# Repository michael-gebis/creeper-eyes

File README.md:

# Frankenstein Head with Animated Eyes

Twin animated eyes for Jose Aveleira's 3D-printed
[Frankenstein head with animated eyes](https://www.printables.com/model/620191-frankenstein-head-with-animated-eyes),
driven by an ESP32 and two 1.5" OLED panels.

The eyes wander, blink and dilate on their own, and keep doing it with nothing
plugged in but power. Everything past that is optional.

## What it does

- **Twenty-five eye designs** — [see them all](docs/EYES.md). One is built in; any other can be
  loaded from a file on the control page, [no rebuild needed](docs/EYE_FILES.md)
- **Watches the room on its own**: wandering gaze, autonomous blinking, pupils
  that dilate
- **Takes direction** from a web page, a serial console or a REST API, so you
  can aim the gaze or fire a startle effect without opening the head
- **Tells the time**, with an analogue clock drawn in the iris
- **Sleeps at night**, so it is not staring at 3am
- **Dims to suit the room**, fading between levels, and switches right off —
  [brightness](docs/BRIGHTNESS.md)
- **Sets itself up from a code on the eye** — point a phone at it and it
  joins the head's network and opens the setup page, with nothing typed
- **Updates over WiFi**, so a sealed head never needs opening again
- **Runs on a generic ESP32** and either colour or greyscale panels

Two panels, one dev board, fourteen wires. If you would rather not have the
wires, there is [a circuit board](hardware/README.md) for it.

## What to buy

### ESP32 board

Any **classic ESP32** (ESP-WROOM-32 module, Xtensa dual core) with 4 MB flash.

> **Not** an ESP32-**S2**, **S3**, **C3** or **C6**. Those are different
> architectures and will not run this build. If your board shows up as USB
> vendor ID `303A`, it is one of those. A classic ESP32 uses a separate
> USB-serial chip — CH340 (`1A86`) or CP210x (`10C4`).

Known good: the 30-pin **DOIT ESP32 DevKit V1**, sold under a dozen names with
"NodeMCU", "ESP32S" and "Type-C" in the title. Roughly $5 each in three-packs.
Either USB-serial chip is fine; CH340 may need a driver on Windows.

### Displays — read this part carefully

Waveshare sells **two different 1.5" 128×128 OLED modules** with nearly
identical names and **identical 7-pin headers**. You cannot tell them apart by
wiring, and the wrong one shows white static.

| Product | Controller | Display | Build to use |
| :------ | :--------- | :------ | :----------- |
| **1.5inch RGB OLED Module** | SSD1351 | 65K colour | `esp32dev` |
| **1.5inch OLED Module** | SSD1327 | 16 greys | `gray` |

Buy **two**. Either works, and the grayscale panels run faster.

Which to get depends on the eyes you want. The artwork was drawn in colour,
and **some designs do not survive the conversion** — anything carrying its
detail in hue rather than in brightness comes out flat. The newt is the worst
of them: its greens and golds land on much the same grey. Others lose nothing
worth having; the default eye in particular looks every bit as good in
sixteen greys as it does in colour.

[docs/EYES.md](docs/EYES.md) renders all 25 designs both ways, side by side,
which is the quickest way to decide.

Both are 3.3 V / 5 V tolerant and need no level shifting.

### Everything else

- Breadboard and male-to-female jumper wires (14 connections)
- USB-C cable — this also carries the serial console
- The printed parts and hardware from the
  [Printables model](https://www.printables.com/model/620191-frankenstein-head-with-animated-eyes)

A plain USB port powers everything comfortably: two panels and the ESP32,
WiFi and all, sit well inside the 500 mA a port supplies.

## Wiring

Six signals are shared by both panels; only chip select differs. Left and
right below are **Frank's own**, so facing him, his right eye is the one on
your left.

| Signal | DevKit pin | Frank's right (your left) | Frank's left (your right) |
| :----- | :--------- | :------------------------ | :------------------------ |
| VCC    | `3V3`      | VCC | VCC |
| GND    | `GND`      | GND | GND |
| DIN    | `D18`      | DIN | DIN |
| CLK    | `D5`       | CLK | CLK |
| DC     | `D33`      | DC  | DC  |
| RST    | `D27`      | RST | RST |
| CS     | `D15` / `D4` | CS ← `D15` | CS ← `D4` |

> **Use `3V3`, never `VIN`.** ESP32 GPIOs are 3.3 V and not 5 V tolerant.

Module silkscreens vary between sellers — `DIN` may be labelled `SDA`, `SI` or
`MOSI`; `CLK` may be `SCL`, `SCK` or `D0`. Match by position, not by letters.

**Full details, assembly order and troubleshooting: [docs/WIRING.md](docs/WIRING.md).**

Optional, and compiled out by default: a **battery-backed clock**, four more
wires onto two otherwise idle pins — [docs/WIRING_RTC.md](docs/WIRING_RTC.md).

### Or a circuit board instead of the jumpers

The same fourteen wires exist as a carrier board in
[hardware/](hardware/README.md): the DevKit plugs into a socket, each eye gets
its own header, and the SPI bus is copper rather than Dupont leads — which
matters mostly because nothing can work loose inside a sealed head. About $10
for five boards.

> **Rev A is tested and works**: a DevKit on one drives two colour panels and a
> DS3231, the clock on jumpers because its header suits a different module
> from the one in use. **Rev B**, which changes that header, is **untested**:
> it passes KiCad's checks, and no board has been made.

## Build and flash

This is a [PlatformIO](https://platformio.org/) project. No Arduino IDE needed,
and nothing to install by hand beyond PlatformIO itself — the Xtensa toolchain,
the ESP32 Arduino core and the Adafruit libraries all download on the first
build.

**New to PlatformIO?** Install the
[PlatformIO IDE extension for VS Code](https://docs.platformio.org/en/latest/integration/ide/vscode.html).
It is the same two steps on Windows, macOS and Linux — install VS Code, then
install the extension — and its Quick Start walks you through building a
blinking LED before you come back here. The extension includes the command
line this page uses, so nothing below is closed off by starting there.

**Happier in a terminal?** Install PlatformIO Core on its own. The
[installation methods](https://docs.platformio.org/en/latest/core/installation/methods/index.html)
page covers all three systems; the short version is:

```sh
uv tool install platformio       # or: pipx install platformio
```

### Environments

| Environment | Builds | Use for |
| :---------- | :----- | :------ |
| `esp32dev` | Eyes, SSD1351 colour | **Default.** Waveshare 1.5inch RGB OLED |
| `gray` | Eyes, SSD1327 grayscale | Waveshare 1.5inch OLED |
| `displaytest` | Solid-colour fills, SSD1351 | Bring-up and fault isolation |
| `probe1327` | Raw SSD1327 init, no library | Identifying an unknown panel |
| `esp32dev_rtc` / `gray_rtc_open` | Eyes plus a battery-backed clock | With a [DS3231 fitted](docs/WIRING_RTC.md) |
| `gray_rtc` | The same, with authentication on | A head left on a network. Needs credentials in `secrets.h` |
| `esp32dev_local` / `gray_local` | Eyes only, no networking | A head with no WiFi — about 695 KB smaller |
| `gray_rtc_ota` / `esp32dev_rtc_ota` | The RTC builds, flashed over WiFi | **Use these** to update an RTC or authenticated head |
| `esp32dev_ota` / `gray_ota` | The plain builds, flashed over WiFi | Updating a sealed head. Using one on an RTC board flashes the RTC and auth away |
| `rtc_probe` | Raw I²C scan and DS3231 read | Bringing up an RTC module |
| `qrtest` / `qrtest_rgb` | QR codes on the panels, grey / colour, no network | Measuring what a phone can read — [Codes on the eyes](docs/QR.md) |

`gray_rtc` is the only environment that requires anything of you before it
will build: `AUTH_USER`, `AUTH_PASS`, `AUTH_TOKEN_VALUE` and `OTA_PASSWORD` in
`include/secrets.h`. It stops with an error naming them rather than producing
an open device. Use `gray_rtc_open` to skip that.

### Commands

```sh
pio run                              # build the default (colour) environment
pio run -e gray -t upload            # build and flash the grayscale build
pio run -e gray -t upload -t monitor # ...and open the console
pio device monitor                   # console only
pio device list                      # find the serial port
```

If the port is picked wrongly, pin it in `platformio.ini` with
`upload_port = COM5` (or `/dev/ttyUSB0`).

## Where to go next

This page gets you a working head. Everything else has a page of its own.

| | |
| :-- | :-- |
| [Wiring](docs/WIRING.md) | Every wire, in order, with what goes wrong |
| [The eyes](docs/EYES.md) | The gallery, choosing designs, the pupil, the startup cards, a panel fitted the wrong way |
| [Eye files](docs/EYE_FILES.md) | One more design, loaded from the control page without a rebuild |
| [Driving it](docs/CONTROL.md) | Web page, serial console, REST API |
| [Networking](docs/NETWORK.md) | Joining WiFi, changing it later, updating over the air |
| [Codes on the eyes](docs/QR.md) | Setup and address codes, and what a phone can really read off a panel |
| [Keeping time](docs/TIME.md) | Time servers, the clock face, running without a network |
| [Brightness](docs/BRIGHTNESS.md) | The dimmer: curves, fades, matching two panels |
| [Sleep mode](docs/SLEEP.md) | Dark panels overnight |
| [Configuring](docs/CONFIG.md) | Every build option, and what gets saved |
| [Locking it down](docs/SECURITY.md) | Passwords, and why there is no HTTPS |
| [A circuit board](hardware/README.md) | The wiring as a PCB — rev A tested, rev B not yet made |
| [Testing](docs/TESTING.md) | The test suite, the soak harness, the tools |
| [Frame rate](docs/FRAME_RATE.md) | How the eyes went from 19 frames a second to 51 on colour, and from 33 to 75 on greyscale |

And two pages that are neither instructions nor reference, but a record of
being wrong in public: [why a 35-byte request took 50 ms](docs/HTTP_LATENCY.md)
and [the battery-backed clock](docs/WIRING_RTC.md).

## Troubleshooting

| Symptom | Cause |
| :------ | :---- |
| **Both panels show white static** | Wrong controller. You have SSD1327 panels and built `esp32dev`, or vice versa. Confirm with `pio run -e probe1327 -t upload -t monitor` — if the panels respond to that, they are SSD1327; build `gray`. |
| Both panels dark | Power, or `D27` (RST) not connected. Check 3V3 and GND at the module pins. |
| One panel dark | That panel's `CS` wire. Everything else is shared, so a shared fault would take out both. |
| Flicker or speckle | Bus integrity. Shorten the `CLK` and `DIN` jumpers, or lower the bus speed: `SSD1351_SPI_HZ` for colour, `SSD1327_SPI_HZ` for greyscale. |
| Garbled serial output | `DEBUG_BAUD` and `monitor_speed` disagree, or a CH340 clone struggling above 115200. |
| Board resets when a panel is connected | Brownout. Use a powered hub or feed 5 V to `VIN`. |
| Board will not boot | Something on `D12`. Held high at reset it stops the ESP32 starting. No eye signal uses it. |
| The web page lags, or an update fails | Almost certainly the radio. Check the signal on the Wi-Fi card — the page says what the number means. Every delay and every failed update measured on this project traced back to packet loss, not to the firmware. `uv run tools/test_api.py --host frank.local --decompose 200` takes the guesswork out of it. |

Frame rate is **not** a useful signal for whether panels are connected — the
SPI writes happen either way, so the rate is the same with nothing attached.

For bring-up, `displaytest` drives each panel alone with solid fills at a
deliberately slow 2 MHz, which separates wiring faults from rendering faults.

## Credits

**The head itself is [Jose Aveleira's](https://www.printables.com/@JoseAveleira_1373378)**
— [Frankenstein head with animated eyes](https://www.printables.com/model/620191-frankenstein-head-with-animated-eyes)
on Printables. None of this has anywhere to live without it.

Firmware lineage, oldest first:

- **[Adafruit Uncanny Eyes](https://learn.adafruit.com/animated-electronic-eyes)** — Phil Burgess / Paint Your Dragon, for Adafruit Industries. The rendering engine and the eye artwork. SPI FIFO insight from Paul Stoffregen's `ILI9341_t3`; concept inspired by David Boccabella (Marcwolf).
- **Laurent Moll**, 2018 — [Uncanny Eyes costume](https://www.hackster.io/projects/376a13/), dual-display ESP32 work.
- **[bitcldr/creeper-eyes](https://github.com/bitcldr/creeper-eyes)** — the PlatformIO project this forks from.
- **[TeensyEyes](https://github.com/chrismiller/TeensyEyes)** — Chris Miller. MIT. 23 of the 25 eye designs are converted from its artwork by [`tools/gen_eyes.py`](tools/gen_eyes.py).
- This fork — generic ESP32 support, grayscale panels, console, splash, diagnostics,
  networking, the control page and API, eye files, the dimmer and the carrier board.

Three bugs fixed here also affect the upstream colour build: an out-of-range
eyelid index that put a teardrop artifact at one eye's edge, a shared reset
line that wiped the first panel's initialisation while the second started, and
a chip-select constant that selected the wrong panel during init.

MIT licensed — see [LICENSE](LICENSE).

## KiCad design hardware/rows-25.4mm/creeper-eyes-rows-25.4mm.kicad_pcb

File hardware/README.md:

# A circuit board for Frank

The breadboard and its fourteen jumper wires, as a printed circuit board: a
carrier that the ESP32 DevKit plugs into, with a header for each eye and one
for the optional clock, and the SPI bus in copper instead of Dupont leads.

> **Rev A is tested and works.** A DevKit plugged into one drives two colour
> panels, with a DS3231 on jumpers — its header suits the ZS-042, not the
> module in use, which is what rev B changes — and without C1. Under long,
> heavy test load on a single USB-C supply it browned out now and then; see
> [Frame rate](../docs/FRAME_RATE.md#brownouts-and-the-cpu-at-160-mhz). Fit C1.
>
> **Rev B is untested.** It passes KiCad's checks — electrical rules,
> schematic against board, design rules — and no board has been made.

## What it is

There are no discrete electronics in this project. The whole thing is three
off-the-shelf modules and the wires between them:

- an ESP32 DevKit V1 (30-pin, 2.54 mm headers)
- two Waveshare 1.5" OLED panels, which share an identical 7-pin header
- optionally, a DS3231 module

So the board is a **carrier**: a socket for the DevKit, a 7-pin header for
each eye, a 5-pin header for the RTC, and the shared SPI bus routed between
them in copper. One capacitor, because the panels' boost converters draw in
bursts and it costs nothing. No active parts, nothing surface-mount, nothing
to calculate. Its job is to replace the breadboard with something that cannot
come loose inside a sealed head.

The wiring is exactly [WIRING.md](../docs/WIRING.md) and
[WIRING_RTC.md](../docs/WIRING_RTC.md):

| Signal | DevKit pin | Goes to |
| :----- | :--------- | :------ |
| 3V3 | `3V3` | both panels, RTC, C1 |
| GND | `GND` | both panels, RTC, C1 |
| DIN | `D18` | both panels |
| CLK | `D5` | both panels |
| DC | `D33` | both panels |
| RST | `D27` | both panels |
| CS | `D15` | Frank's right panel (J3, your left) |
| CS | `D4` | Frank's left panel (J4, your right) |
| SDA | `D21` | RTC |
| SCL | `D22` | RTC |

72 × 56 mm, two layers, four M3 mounting holes. The DevKit plugs in with its
USB connector towards the bottom edge and its antenna end flush with the top
edge — the antenna section overhangs by about half a millimetre, and there
is no copper anywhere near it in any case. Every socket pin is labelled with the
DevKit's own name for it, and each eye connector says whose eye it is in
both senses, so a board sitting on the bench answers the question the wiring
guide spends a page on.

The panels connect by cable — a 7-wire Dupont lead or a JST-XH pigtail onto
each header — because they live in the head's eye sockets, not on the board.
The RTC header takes the five-pin "DS3231 mini" module sold for the Raspberry
Pi, which plugs straight onto it: `VCC SDA SCL NC GND` from top to bottom,
matching the module's own `+ D C NC -`, with GND on the bottom pin. Any other
module goes on by four wires to the labelled pins.

## Revisions

**Rev B**, current, untested: J5, the RTC header, is five pins in the order of the
DS3231 mini module (`VCC SDA SCL NC GND`, rows 12–16) instead of six in the
ZS-042's (`32K SQW SCL SDA VCC GND`, rows 12–17). SCL keeps its route; SDA,
VCC and GND each come in on a different row. Nothing else moved.

**Rev A**, the first order, tested and working: the mini module does not plug
onto J5. Wire it
by name instead — four jumpers, module `+`→`VCC`, `D`→`SDA`, `C`→`SCL`,
`-`→`GND` — and leave J5's `32K` and `SQW` empty. Power off first: the
firmware only looks for the RTC at boot.

## What it costs

| | Five boards | Per board |
| :-- | :-- | :-- |
| JLCPCB or PCBWay, 2-layer, 72 × 56 mm | ~$2 fabrication, $2–5 slow shipping (~$20 by courier if impatient) | under $2 |
| Two 1×15 female headers, 2.54 mm — the DevKit socket | ~$1 | |
| Two 1×7 and one 1×5 male pin headers, 2.54 mm | ~$1 | |
| C1, electrolytic, 5 mm diameter, 2 mm lead pitch: 10 µF works, but take the largest that comes in a 5 mm can, typically 22 or 47 µF | pennies | |

**About $10 for five boards, all in**, and one to two weeks. The DevKit and
the displays you already own plug into it.

The other tier — an integrated board with the ESP32-WROOM module soldered
down, USB-C, a CH340 and a regulator, assembled at the fab — comes to $8–15 a
board in small quantities plus setup fees, and buys nothing over the $5 DevKit
except a slimmer profile and the loss of "unplug it and swap it". Not worth
it. This is a carrier board.

## Two boards, because there are two DevKits

Along each row the pins are on 2.54 mm centres on every board — that is the
header strip itself, and nobody gets it wrong. The distance *between* the two
rows is the clone maker's own choice, and it varies. So the design is one and
the boards are two, in directories named for the number:

| Directory | Row pitch | For |
| :-- | :-- | :-- |
| `rows-25.10mm/` | 25.10 mm | The author's DevKit, a 30-pin "DevKit V1" clone, measured |
| `rows-25.4mm/` | 25.4 mm (1.0") | The DOIT reference design and clones that follow it |

Each holds its own KiCad project, a `gerbers/creeper-eyes-rows-…-gerbers.zip`
to upload, and renders. The pitch is printed on both sides of the board, so
five of each can sit in a drawer without confusion.

## Before ordering: two things to check against your DevKit

Both are things a datasheet cannot settle, because "ESP32 DevKit V1" is a
name a dozen factories use.

1. **The row pitch.** Measure across both rows of pins with calipers, at
   the base of the pins where they enter the plastic rather than at the
   tips, which are often toed in. Take the outside-to-outside and the
   inside-to-inside readings: their average is the centre-to-centre pitch,
   and their difference should be one pin width (~0.64 mm), which tells you
   the measurement is sound. The author's board read 25.72 and 24.48, so
   25.10. Order the variant that matches; if neither does, add a line to
   `VARIANTS` in `gen_board.py` and regenerate (below). Half the board moves
   with it; nothing needs redrawing.
2. **The pinout.** Hold the DevKit with the USB connector towards you,
   components up. The left row should read `EN VP VN D34 D35 D32 D33 D25 D26
   D27 D14 D12 D13 GND VIN` top to bottom, and the right row `D23 D22 TX0 RX0
   D21 D19 D18 D5 TX2 RX2 D4 D2 D15 GND 3V3`. That is what the board's
   silkscreen says beside each socket pin, so a mismatch is a matter of
   holding the two next to each other. If a pin differs, `DEVKIT_LEFT` and
   `DEVKIT_RIGHT` in `gen_board.py` are where to say so.

Then two things worth knowing that are not risks: the pads are square for
pin 1 of every connector, and C1's footprint carries a `+` mark on the
silkscreen — the longer lead of the capacitor goes there.

## Ordering

Upload the zip from the matching variant's `gerbers/` directory to
[JLCPCB](https://jlcpcb.com) or [PCBWay](https://www.pcbway.com). The defaults are right: 2 layers, 1.6 mm,
HASL, any colour, quantity 5. Nothing on the board comes near a design rule —
the narrowest anything gets is 0.25 mm tracks and about 0.3 mm of clearance,
against minimums of 0.127.

Solder the two 15-pin sockets first, using the DevKit itself as a jig to keep
them parallel: plug the sockets onto the DevKit, drop the assembly into the
board, solder, unplug. Then the pin headers, then C1.

## How it was made, and how to change it

The board is generated by a script rather than drawn, because the one
dimension that has to be measured moves half the layout.

Both scripts run with the Python *inside* KiCad, not the system one, because
the layout is built through KiCad's own `pcbnew` module. Where that lives:

| | |
| :-- | :-- |
| Windows | `%LOCALAPPDATA%\Programs\KiCad\<version>\bin\python.exe` |
| macOS | `/Applications/KiCad/KiCad.app/Contents/Frameworks/Python.framework/Versions/Current/bin/python3` |
| Linux | the system `python3`, with KiCad's packages installed |

```sh
"$KICAD_PYTHON" hardware/gen_board.py     # writes every variant
"$KICAD_PYTHON" hardware/make_outputs.py  # checks and exports each
```

Either takes a pitch as an argument to do just one: `gen_board.py 25.4`.

Needs [KiCad](https://www.kicad.org/) 9 or later — the author used 10.
`gen_board.py` holds the netlist as one table and the routing as a list of
coordinates on a 2.54 mm grid, with everything right of the DevKit's left row
placed relative to the pitch; `make_outputs.py` runs the electrical rule
check, compares the schematic's netlist with the board's pad by pad, runs the
design rule check with schematic parity, and only then exports the Gerbers
and the renders. All three pass clean for both variants at the moment.

Editing in KiCad directly also works — it is an ordinary project — but a
regeneration will overwrite it, so a change worth keeping belongs in the
script.

The DevKit's footprint and the three symbols with meaningful pin names live in
each variant's `.pretty/` directory and `.kicad_sym` file, which its library
tables point at.

## Not on the board

Kept off deliberately, and cheap to add if there is ever a reason:

- a header breaking out the unused pins (`D23`, `D25`, `D26`, `D32`, `D34`,
  `D35`, …) for sensors. Not `D19`: the firmware hands it to the SPI
  peripheral as MISO in `SPI.begin(SCLK_PIN, MISO_PIN, MOSI_PIN)`, and
  although nothing is ever read back — the panels are write-only — the
  peripheral is attached to the pin all the same. Passing `-1` there instead
  would genuinely free it, and is the change to make before breaking it out.
- a photocell, which upstream Uncanny Eyes uses to drive dilation. A light
  sensor for the [dimmer](../docs/BRIGHTNESS.md) is on the
  [TODO list](../TODO.md#a-light-sensor-for-automatic-brightness), and the
  unused `D34`, `D35`, `VP` and `VN` are where it would go
- a ground pour — at 8 MHz on a 7 cm board, with the breadboard already
  working, it would be decoration

## Files

| | |
| :-- | :-- |
| `gen_board.py` | The design, as a script. Edit this. |
| `make_outputs.py` | Checks, Gerbers, renders |
| `rows-25.10mm/`, `rows-25.4mm/` | One directory per DevKit row pitch, each containing: |
| `  creeper-eyes-rows-…mm.kicad_pro` / `.kicad_sch` / `.kicad_pcb` | The KiCad project the script writes |
| `  creeper-eyes-rows-…mm.pretty/`, `.kicad_sym` | Project footprint and symbol libraries |
| `  gerbers/creeper-eyes-rows-…mm-gerbers.zip` | What the fab wants |
| `  images/` | Renders of both sides, and the schematic as a PDF |

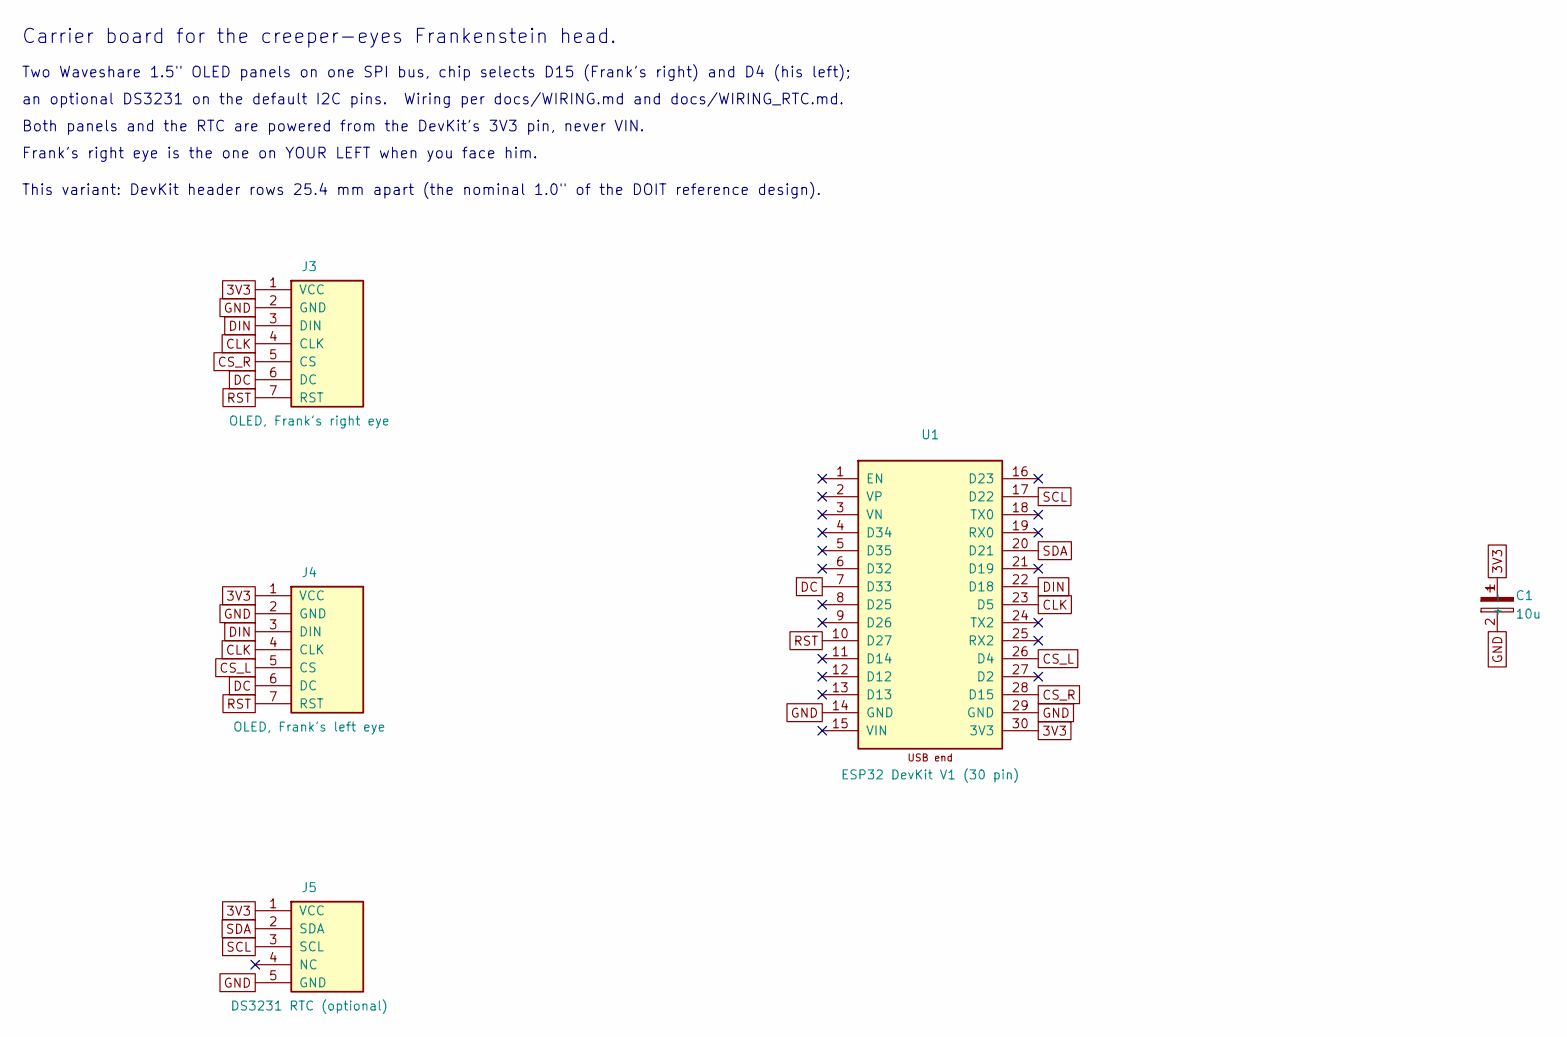
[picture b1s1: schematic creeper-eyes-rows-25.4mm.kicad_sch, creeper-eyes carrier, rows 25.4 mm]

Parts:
C1: 10u; CP_Radial_D5.0mm_P2.00mm
J3: OLED, Frank's right eye; PinHeader_1x07_P2.54mm_Vertical
J4: OLED, Frank's left eye; PinHeader_1x07_P2.54mm_Vertical
J5: DS3231 RTC (optional); PinHeader_1x05_P2.54mm_Vertical
U1: ESP32 DevKit V1 (30 pin); ESP32_DevKit_V1_30pin

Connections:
3V3: C1.1 (+), J3.1 (VCC), J4.1 (VCC), J5.1 (VCC), U1.30 (3V3)
CLK: J3.4 (CLK), J4.4 (CLK), U1.23 (D5)
CS_L: J4.5 (CS), U1.26 (D4)
CS_R: J3.5 (CS), U1.28 (D15)
DC: J3.6 (DC), J4.6 (DC), U1.7 (D33)
DIN: J3.3 (DIN), J4.3 (DIN), U1.22 (D18)
GND: C1.2 (-), J3.2 (GND), J4.2 (GND), J5.5 (GND), U1.14 (GND), U1.29 (GND)
RST: J3.7 (RST), J4.7 (RST), U1.10 (D27)
SCL: J5.3 (SCL), U1.17 (D22)
SDA: J5.2 (SDA), U1.20 (D21)

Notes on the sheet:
Carrier board for the creeper-eyes Frankenstein head.
Two Waveshare 1.5" OLED panels on one SPI bus, chip selects D15 (Frank's right) and D4 (his left);
an optional DS3231 on the default I2C pins. Wiring per docs/WIRING.md and docs/WIRING_RTC.md.
Both panels and the RTC are powered from the DevKit's 3V3 pin, never VIN.
Frank's right eye is the one on YOUR LEFT when you face him.
This variant: DevKit header rows 25.4 mm apart (the nominal 1.0" of the DOIT reference design).

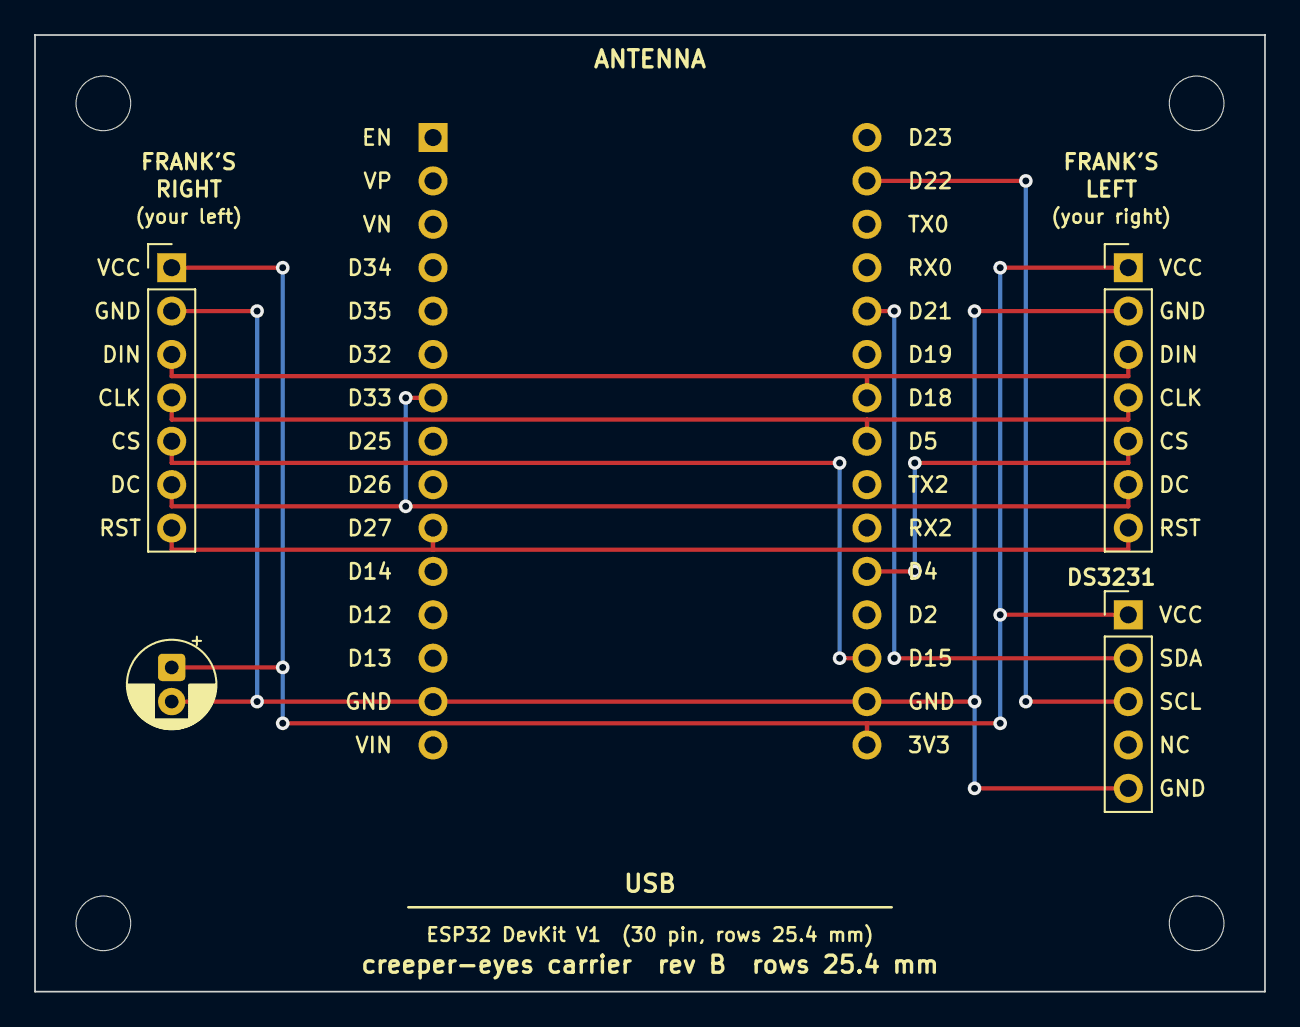
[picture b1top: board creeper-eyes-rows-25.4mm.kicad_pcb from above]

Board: 2 copper layers, 72.0 x 56.0 mm, 9 parts (0 on the bottom side), 10 nets.

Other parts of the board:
H1, H2, H3, H4: M3; MountingHole_3.2mm_M3
